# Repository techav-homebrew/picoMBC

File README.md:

# picoMBC

picoMBC is a generic Pi Pico expansion card for the Sanyo MBC-1000 computer. The primary goal is to add an SD card interface for mass storage, but with some available I/O for future or alternate use.

The MBC-1000 expansion interface is a buffered breakout of the Z80 I/O interface. It does not provide the upper 8 bits of the Z80 address bus or signals required for memory space addressing or DMA. To save I/O, picoMBC multiplexes the 8-bit data and address busses.

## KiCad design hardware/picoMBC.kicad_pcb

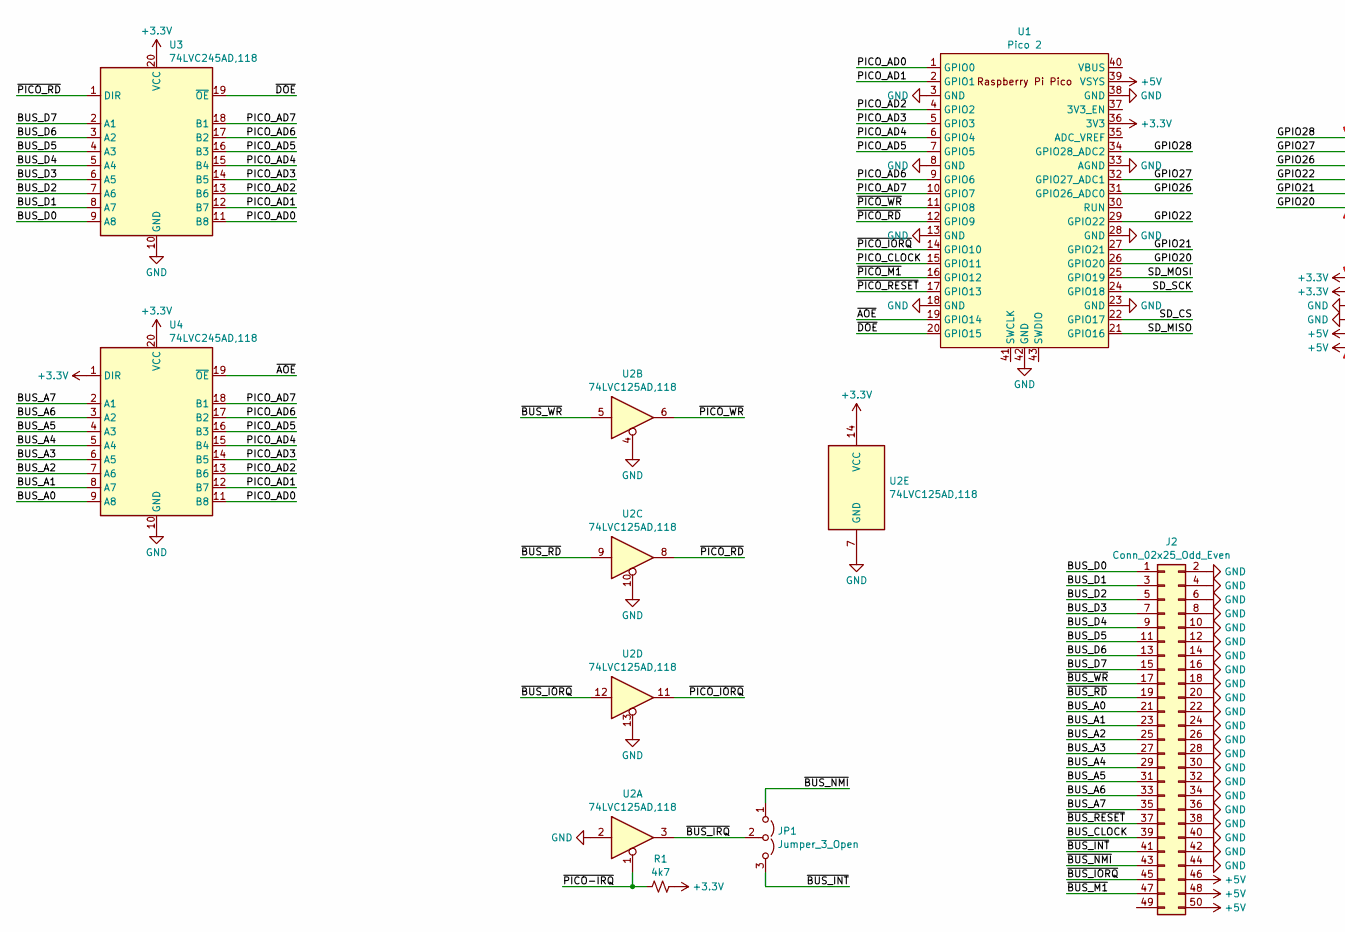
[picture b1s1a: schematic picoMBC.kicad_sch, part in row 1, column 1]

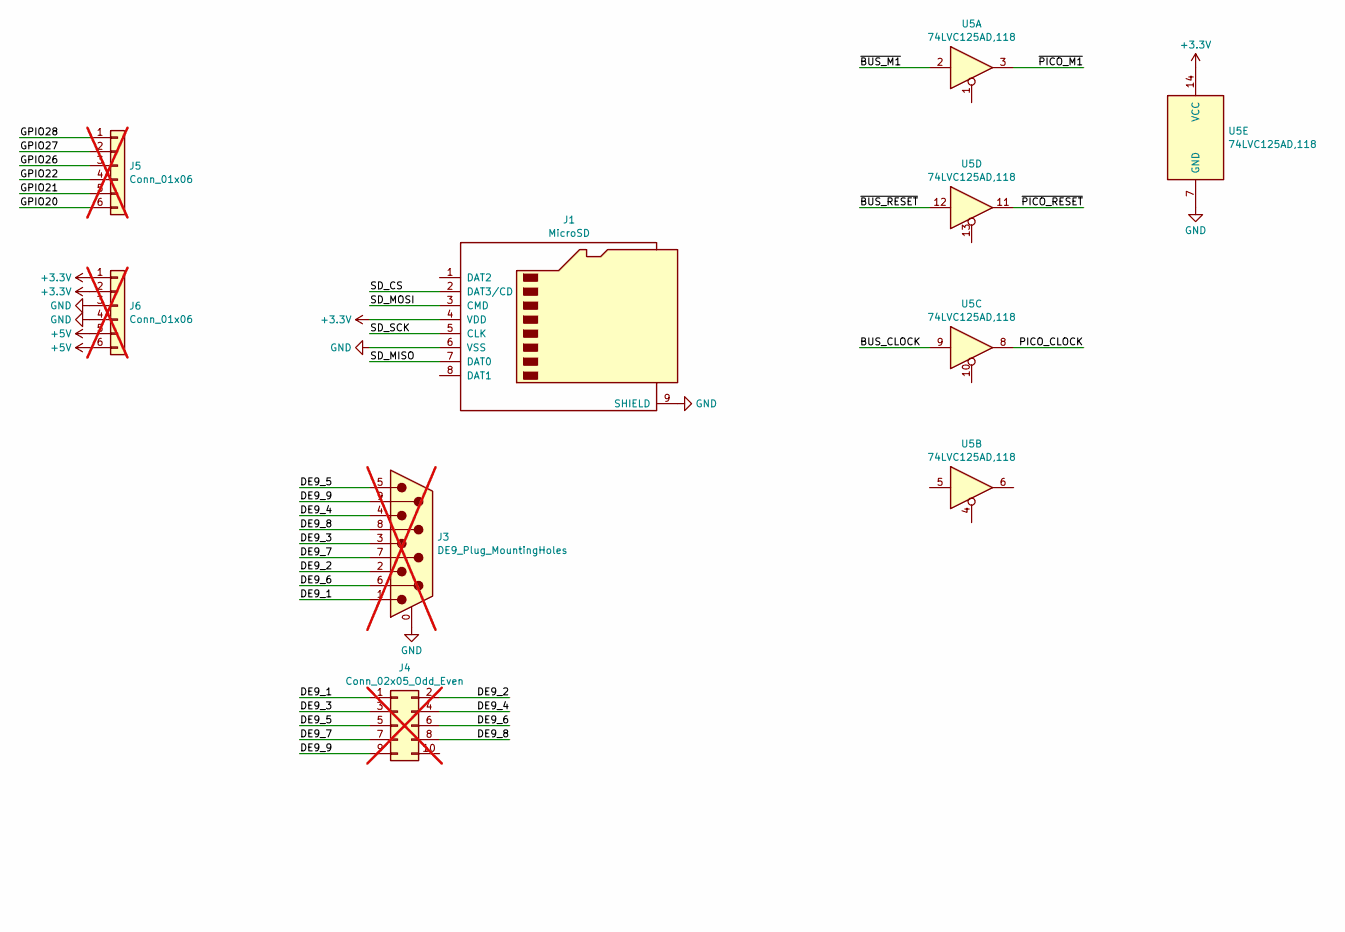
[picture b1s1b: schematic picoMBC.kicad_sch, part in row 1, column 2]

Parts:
J1: MicroSD; microSD_HC_Molex_47219-2001
J2: Conn_02x25_Odd_Even; PinHeader_2x25_P2.54mm_Horizontal
J3: DE9_Plug_MountingHoles; DSUB-9_Male_Horizontal_P2.77x2.84mm_EdgePinOffset4.94mm_Hou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; not fitted
J4: Conn_02x05_Odd_Even; PinHeader_2x05_P2.54mm_Vertical; not fitted
J5, J6: Conn_01x06; PinHeader_1x06_P2.54mm_Vertical; not fitted
JP1: Jumper_3_Open; PinHeader_1x03_P2.54mm_Vertical
R1: 4k7; R_Axial_DIN0204_L3.6mm_D1.6mm_P7.62mm_Horizontal
U1: Pico 2; RPi_Pico_SMD_TH
U2, U5: 74LVC125AD,118; SOIC-14_3.9x8.7mm_P1.27mm; Mouser 771-74LVC125AD-T
U3, U4: 74LVC245AD,118; SOIC-20W_7.5x12.8mm_P1.27mm; Mouser 771-74LVC245AD-T

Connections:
+3.3V: J1.4 (VDD), J6.1, J6.2, R1.1, U1.36 (3V3), U2.14 (VCC), U3.20 (VCC), U4.1 (DIR), U4.20 (VCC), U5.14 (VCC)
+5V: J2.46, J2.48, J2.50, J6.5, J6.6, U1.39 (VSYS)
/BUS_A0: J2.21, U4.9 (A8)
/BUS_A1: J2.23, U4.8 (A7)
/BUS_A2: J2.25, U4.7 (A6)
/BUS_A3: J2.27, U4.6 (A5)
/BUS_A4: J2.29, U4.5 (A4)
/BUS_A5: J2.31, U4.4 (A3)
/BUS_A6: J2.33, U4.3 (A2)
/BUS_A7: J2.35, U4.2 (A1)
/BUS_CLOCK: J2.39, U5.9
/BUS_D0: J2.1, U3.9 (A8)
/BUS_D1: J2.3, U3.8 (A7)
/BUS_D2: J2.5, U3.7 (A6)
/BUS_D3: J2.7, U3.6 (A5)
/BUS_D4: J2.9, U3.5 (A4)
/BUS_D5: J2.11, U3.4 (A3)
/BUS_D6: J2.13, U3.3 (A2)
/BUS_D7: J2.15, U3.2 (A1)
/DE9_1: J3.1, J4.1
/DE9_2: J3.2, J4.2
/DE9_3: J3.3, J4.3
/DE9_4: J3.4, J4.4
/DE9_5: J3.5, J4.5
/DE9_6: J3.6, J4.6
/DE9_7: J3.7, J4.7
/DE9_8: J3.8, J4.8
/DE9_9: J3.9, J4.9
/GPIO20: J5.6, U1.26 (GPIO20)
/GPIO21: J5.5, U1.27 (GPIO21)
/GPIO22: J5.4, U1.29 (GPIO22)
/GPIO26: J5.3, U1.31 (GPIO26_ADC0)
/GPIO27: J5.2, U1.32 (GPIO27_ADC1)
/GPIO28: J5.1, U1.34 (GPIO28_ADC2)
/PICO_AD0: U1.1 (GPIO0), U3.11 (B8), U4.11 (B8)
/PICO_AD1: U1.2 (GPIO1), U3.12 (B7), U4.12 (B7)
/PICO_AD2: U1.4 (GPIO2), U3.13 (B6), U4.13 (B6)
/PICO_AD3: U1.5 (GPIO3), U3.14 (B5), U4.14 (B5)
/PICO_AD4: U1.6 (GPIO4), U3.15 (B4), U4.15 (B4)
/PICO_AD5: U1.7 (GPIO5), U3.16 (B3), U4.16 (B3)
/PICO_AD6: U1.9 (GPIO6), U3.17 (B2), U4.17 (B2)
/PICO_AD7: U1.10 (GPIO7), U3.18 (B1), U4.18 (B1)
/PICO_CLOCK: U1.15 (GPIO11), U5.8
/SD_CS: J1.2 (DAT3/CD), U1.22 (GPIO17)
/SD_MISO: J1.7 (DAT0), U1.21 (GPIO16)
/SD_MOSI: J1.3 (CMD), U1.25 (GPIO19)
/SD_SCK: J1.5 (CLK), U1.24 (GPIO18)
/~AOE: U1.19 (GPIO14), U4.19 (~OE)
/~BUS_INT: J2.41, JP1.3 (B)
/~BUS_IORQ: J2.45, U2.12
/~BUS_IRQ: JP1.2 (C), U2.3
/~BUS_M1: J2.47, U5.2
/~BUS_NMI: J2.43, JP1.1 (A)
/~BUS_RD: J2.19, U2.9
/~BUS_RESET: J2.37, U5.12
/~BUS_WR: J2.17, U2.5
/~DOE: U1.20 (GPIO15), U3.19 (~OE)
/~PICO-IRQ: R1.2, U2.1
/~PICO_IORQ: U1.14 (GPIO10), U2.11
/~PICO_M1: U1.16 (GPIO12), U5.3
/~PICO_RD: U1.12 (GPIO9), U2.8, U3.1 (DIR)
/~PICO_RESET: U1.17 (GPIO13), U5.11
/~PICO_WR: U1.11 (GPIO8), U2.6
GND: J1.6 (VSS), J1.9 (SHIELD), J2.2, J2.4, J2.6, J2.8, J2.10, J2.12, J2.14, J2.16, J2.18, J2.20, J2.22, J2.24, J2.26, J2.28, J2.30, J2.32, J2.34, J2.36, J2.38, J2.40, J2.42, J2.44, J3.0 (PAD), J6.3, J6.4, U1.3 (GND), U1.8 (GND), U1.13 (GND), U1.18 (GND), U1.23 (GND), U1.28 (GND), U1.33 (AGND), U1.38 (GND), U1.42 (GND), U2.2, U2.4, U2.7 (GND), U2.10, U2.13, U3.10 (GND), U4.10 (GND), U5.7 (GND)

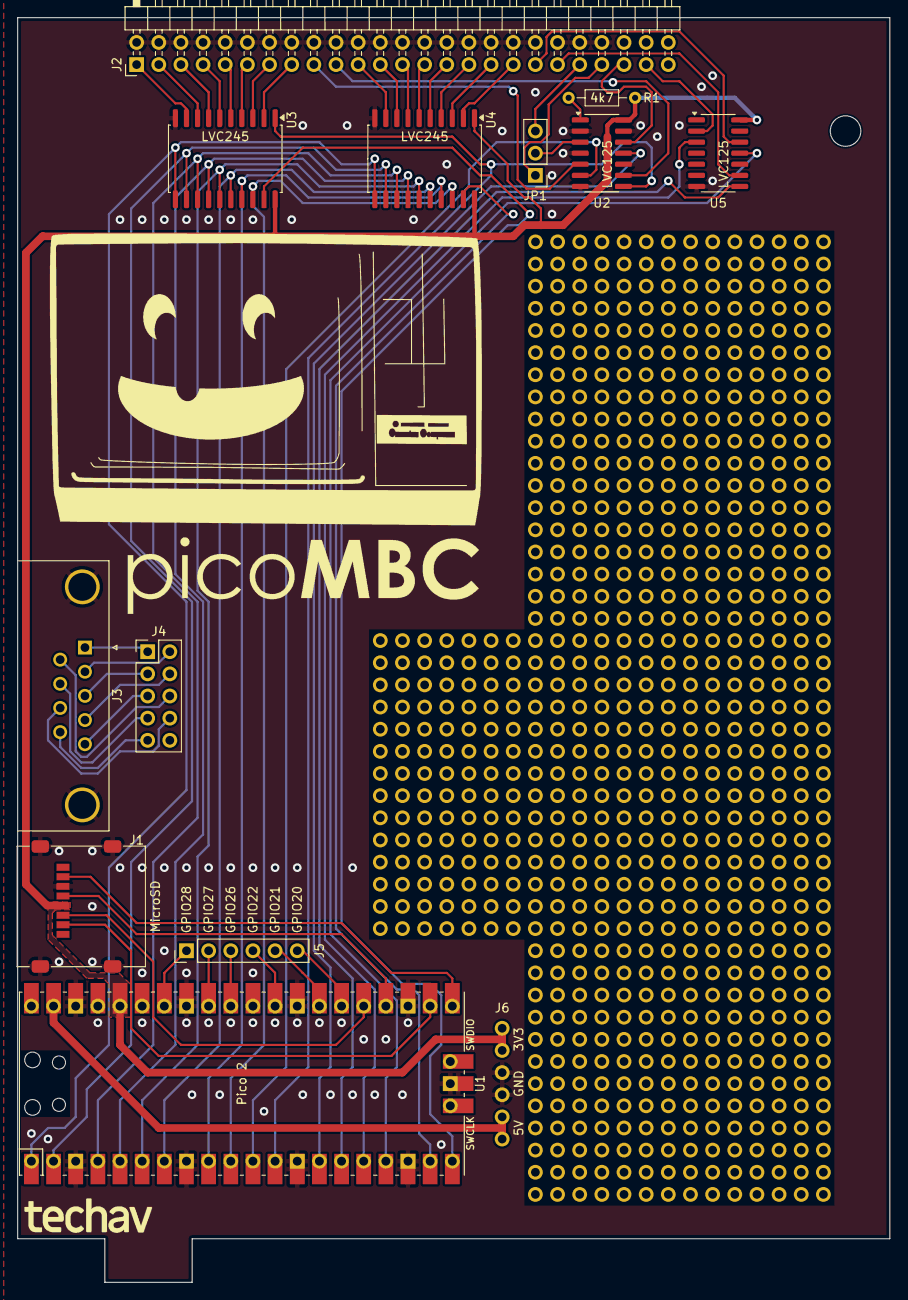
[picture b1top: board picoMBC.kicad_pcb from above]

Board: 2 copper layers, 100.0 x 145.0 mm, 13 parts (0 on the bottom side), 64 nets.

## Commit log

2024-11-17 Multiplex pico bus
    - add buffers to multiplex Pico bus to free up some I/O for future use
2024-11-17 Add readme
2024-11-27 add power header & plot gerbers
